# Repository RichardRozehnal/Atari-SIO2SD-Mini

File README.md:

# Atari SIO2SD Mini

Atari SIO2SD Mini je zařízení, které vám umožní nahrávat programy a hry do Atari přes SIO konektor z MicroSD karty.
Podporuje soubory ATR, XEX, COM a XFD.

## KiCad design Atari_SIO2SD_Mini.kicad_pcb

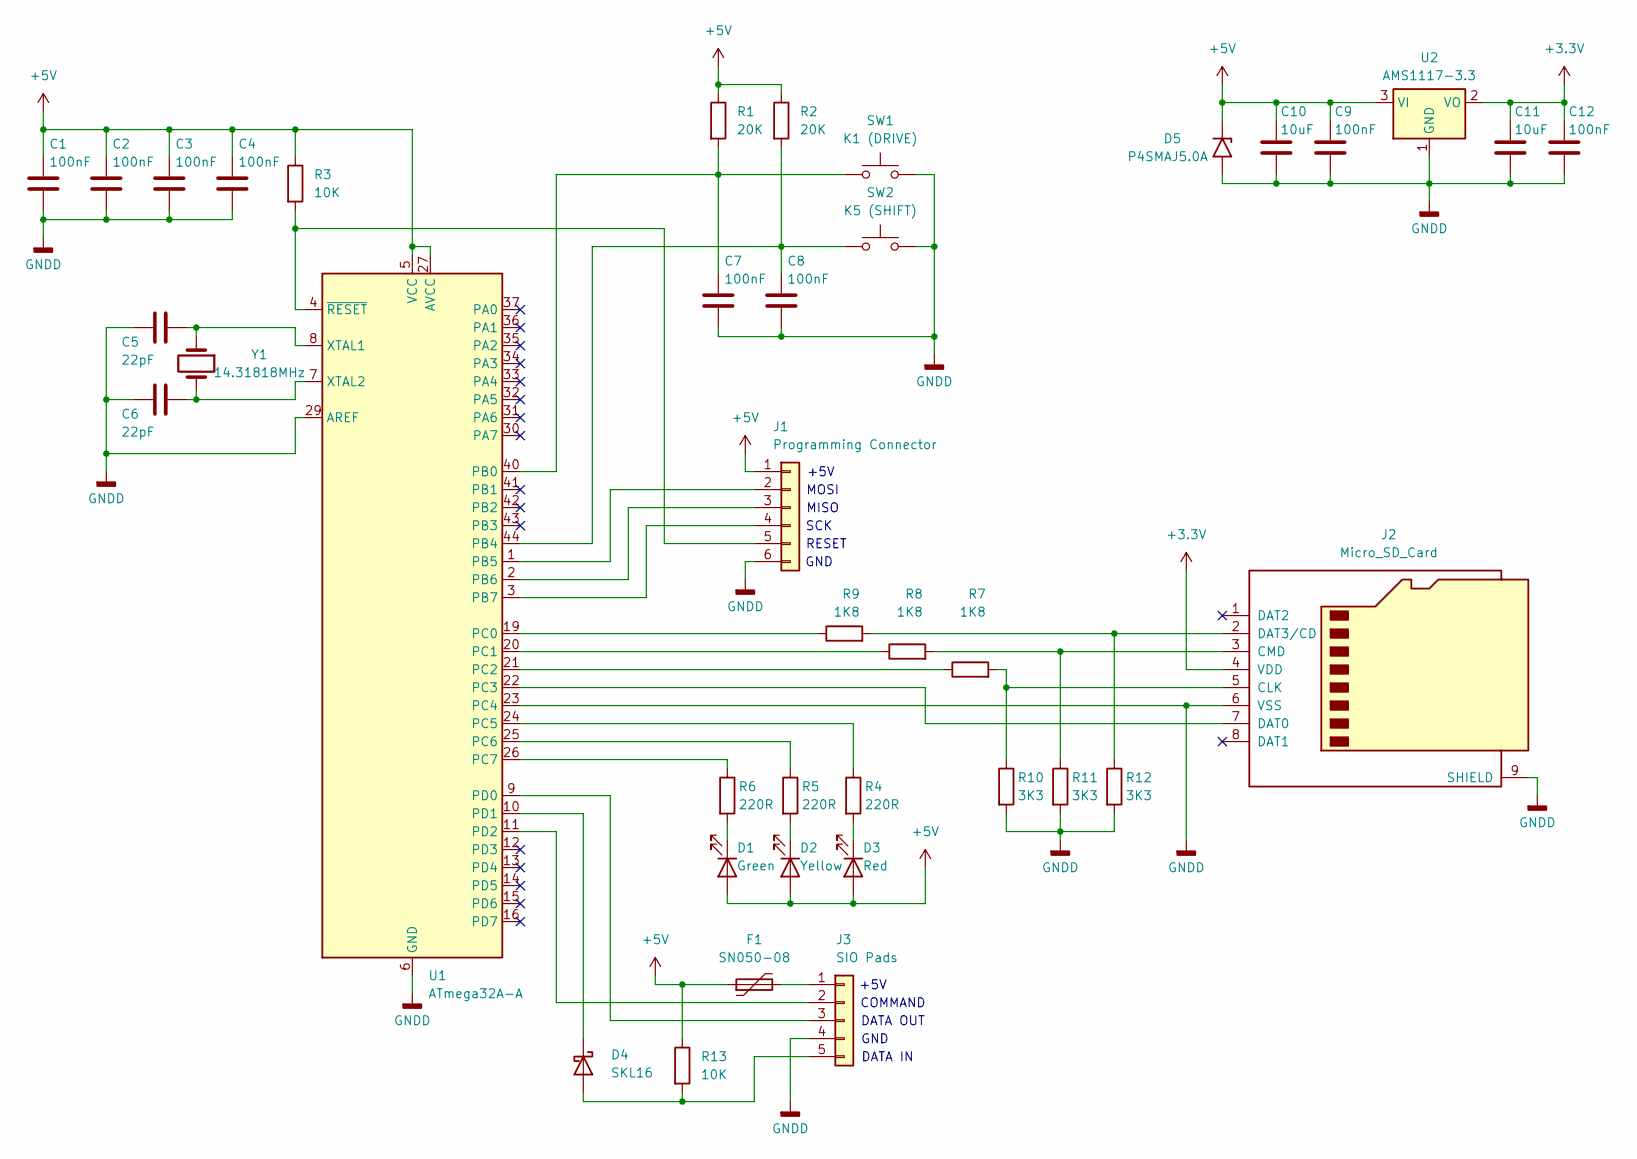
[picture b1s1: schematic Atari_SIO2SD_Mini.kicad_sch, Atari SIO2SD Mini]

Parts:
C1, C2, C3, C4, C7, C8, C9, C12: 100nF; C_1206_3216Metric
C5, C6: 22pF; C_1206_3216Metric
C10, C11: 10uF; C_1206_3216Metric
D1: Green; LED_D3.0mm
D2: Yellow; LED_D3.0mm
D3: Red; LED_D3.0mm
D4: SKL16; D_SOD-123F
D5: P4SMAJ5.0A; D_SMA
F1: SN050-08; Fuse_1206_3216Metric
J1: Programming Connector; PinHeader_1x06_P2.54mm_Vertical
J2: Micro_SD_Card; microSD_HC_Molex_104031-0811
J3: SIO Pads; PinHeader_1x05_P2.54mm_Vertical
R1, R2: 20K; R_1206_3216Metric
R3, R13: 10K; R_1206_3216Metric
R4, R5, R6: 220R; R_1206_3216Metric
R7, R8, R9: 1K8; R_1206_3216Metric
R10, R11, R12: 3K3; R_1206_3216Metric
SW1: K1 (DRIVE); SW_PUSH_6mm_H12mm
SW2: K5 (SHIFT); SW_PUSH_6mm_H12mm
U1: ATmega32A-A; TQFP-44_10x10mm_P0.8mm
U2: AMS1117-3.3; SOT-223-3_TabPin2
Y1: 14.31818MHz; Crystal_HC49-4H_Vertical

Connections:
+3.3V: C11.1, C12.1, J2.4 (VDD), U2.2 (VO)
+5V: C1.1, C2.1, C3.1, C4.1, C9.1, C10.1, D1.2 (A), D2.2 (A), D3.2 (A), D5.1 (A1), F1.1, J1.1, R1.1, R2.1, R3.1, R13.1, U1.5 (VCC), U1.17 (VCC), U1.27 (AVCC), U1.38 (VCC), U2.3 (VI)
GNDD: C1.2, C2.2, C3.2, C4.2, C5.2, C6.2, C7.2, C8.2, C9.2, C10.2, C11.2, C12.2, D5.2 (A2), J1.6, J2.6 (VSS), J2.9 (SHIELD), J3.4, R10.2, R11.2, R12.2, SW1.2, SW2.2, U1.6 (GND), U1.18 (GND), U1.23 (PC4), U1.28 (GND), U1.29 (AREF), U1.39 (GND), U2.1 (GND)
unnamed: D1.1 (K), R6.2
unnamed: D2.1 (K), R5.2
unnamed: D3.1 (K), R4.2
unnamed: D4.2 (A), J3.5, R13.2
unnamed: D4.1 (K), U1.10 (PD1)
unnamed: J1.2, U1.1 (PB5)
unnamed: J1.3, U1.2 (PB6)
unnamed: J1.4, U1.3 (PB7)
unnamed: J1.5, R3.2, U1.4 (~RESET)
unnamed: J2.5 (CLK), R7.2, R10.1
unnamed: J2.3 (CMD), R8.2, R11.1
unnamed: J2.7 (DAT0), U1.22 (PC3)
unnamed: J2.2 (DAT3/CD), R9.2, R12.1
unnamed: F1.2, J3.1
unnamed: J3.2, U1.11 (PD2)
unnamed: J3.3, U1.9 (PD0)
unnamed: C7.1, R1.2, SW1.1, U1.40 (PB0)
unnamed: C8.1, R2.2, SW2.1, U1.44 (PB4)
unnamed: R9.1, U1.19 (PC0)
unnamed: R8.1, U1.20 (PC1)
unnamed: R7.1, U1.21 (PC2)
unnamed: R4.1, U1.24 (PC5)
unnamed: R5.1, U1.25 (PC6)
unnamed: R6.1, U1.26 (PC7)
unnamed: C5.1, U1.8 (XTAL1), Y1.1
unnamed: C6.1, U1.7 (XTAL2), Y1.2

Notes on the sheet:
+5V
GND
RESET
MOSI
MISO
DATA OUT
DATA IN
COMMAND
+5V
SCK

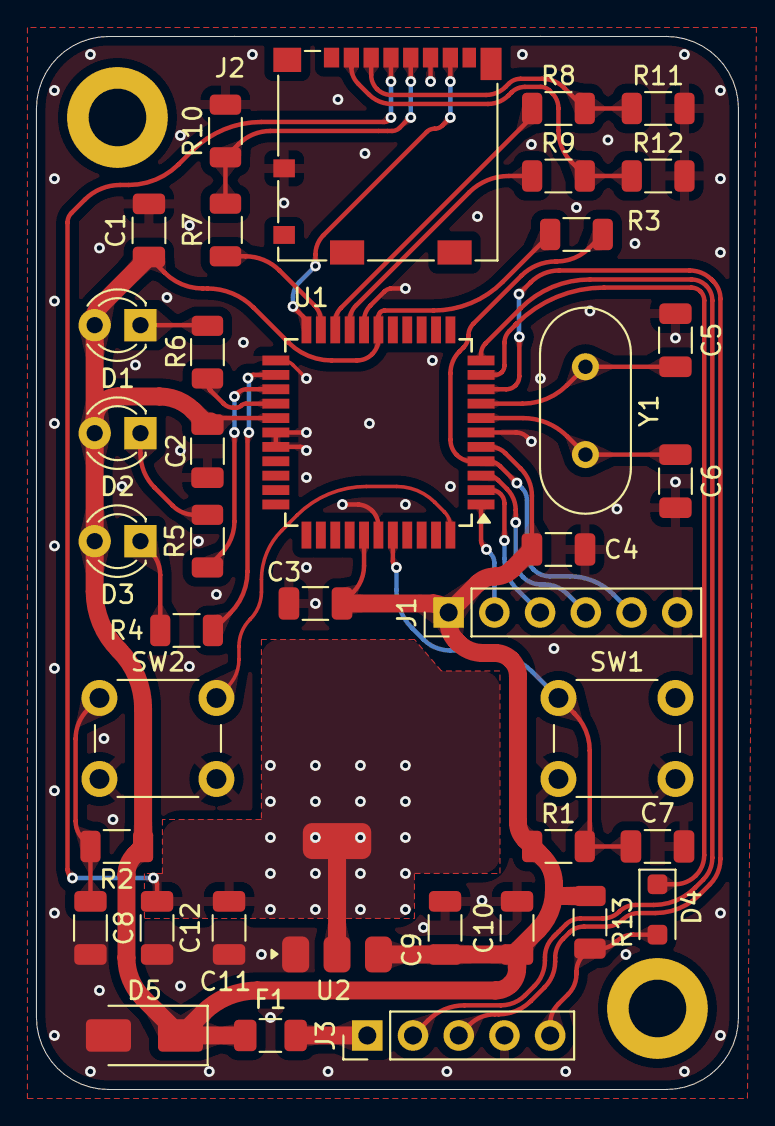
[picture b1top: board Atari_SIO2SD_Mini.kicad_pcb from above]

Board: 2 copper layers, 39.0 x 58.5 mm, 39 parts (0 on the bottom side), 29 nets.

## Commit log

2024-11-28 Create a
